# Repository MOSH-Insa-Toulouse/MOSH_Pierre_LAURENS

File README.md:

# Projet Smart Device
# MICRO-CONTROLEURS ET OPEN-SOURCE HARDWARE:
# Projet de Construction d'un capteur de gaz 
>LAURENS [Pierre](mailto:plaurens@etud.insa-toulouse.fr) - TOUZANI Ismail - Krishna Sujan

<a href="./README_EN.md">Version Anglaise</a>

Ce projet, faisant partie du Master 5ISS de l'INSA Toulouse, a été developpé dans le but de créer un capteur de gas intelligent capable de détecter plusieurs types de gas qui pourront être dangereux pour la santé humaine.
Après avoir construit le capteur dans l'atelier AIME de l'INSA, il sera donc nécessaire de le régler pour en extraire les informations utiles: cela se fera grâce au logiciel LTSpice IV pour la partie éléctronique analogique. Ensuite, et afin de récupérer les données du capteur et les communiquer à travers le réseau LoRA, on utilisera une carte Arduino Uno et une puce RN2483. Enfin, nous utiliserons le logiciel KiCAD pour effectuer le schéma adéquat du câblage entre les différents composants.

# Contenu du Projet
Le projet est constitué des répertoires suivants:
-   **Mosh (Arduino IDE)**: Contient les fichiers des tps effectués en utilisant l'IDE d'Arduino ainsi que les fichiers du projet.

-   **KiCAD**: Contient les fichiers nécessaires à la réalisation du PCB.
Ce fichier est composé de 3 dossiers.
    - **Projet Kicad** : contenant la première version de notre projet.
    - **Projet Kicad plan de masse** : contenant le même projet que le fichier ci-dessus mais avec la réalisation du plan de masse.
    - **Projet Kicad Aime plan de masse** : contenant le PCB du capteur de Gaz réalisé dans les locaux du AIME.

-   **LTSpice**: Contient les fichiers nécessaires à la partie éléctronique analogique.

-  **Manufacturing_Kicad**: Dossier contenant le fichier de création de la carte.

### Partie collection de données et communication LoRA: 
Dans cette partie, nous avons testé la collection de données et communication LoRA avec un capteur de test:

Ci-dessus l'image du montage permettant d'interconnecter le module LoRa, l'Arduino UNO et le capteur de Gaz.
Ci-dessous une série d'images montrant le résultat de notre montage avec la réception et l'envoi de la valeur du capteur.

### Partie construction du shield/PCB: 
Dans cette partie, nous avons construit notre propre shield/PCB grâce à KiCAD :

Un Zoom sur la conception du capteur de Gaz AIME sur Eeschema:

Puis ci-dessous, l'ensemble du Capteur Intelligent designé sur Eeschema:

Conception du layout avec le traçage des routes et la création des footprints et leur positionnement sur la carte.

Nous avons réalisé un plan de masse pour réduire la consommation en cuivre et limiter le routage en une seule couche. En effet, nous avons  supprimé toutes les routes sur la couche avant de notre shield(rouge) présentent sur la photo ci-dessus.
Le plan de masse permet également de réaliser le routage sur une seule couche, la couche arrière  de notre Shield. Pour finir, nous avons ainsi respecté les contraintes de routage définies par l'INSA.

### Partie électronique analogique: 
Concernant cette partie, nous avons étudier, en utilisant LTSPice IV, la partie électronique analogique du module Smart Device où nous serons amené à mesurer la résistance, le faible courant avec un microcontrôleur et effectuer un filtrage passe bas pour extraire les informations utiles de notre capteur de gaz. 

<a href="/LTspice/UF_Smart_Device_ Partie_analogique_avec_LTSpice_IV.pdf">Rapport_LTSPice</a>

### Choix de Conception

 - Nous avons modifié la forme du contour du shield en un rectangle plus grand que l'Arduino UNO pour faciliter le routage et l'inclusion de la puce LoRa.

- Au niveau du PCB, nous avons du faire face à des avertissements de type "Pad près d'un pad" au moment de la validation de notre PCB. Nous avons remarqué que ces messages ciblés les capacités que nous avons choisi dans les librairies génériques qui se sont avérés plus petites que ceux que nous utiliserons en réalité. Les marges de pistes sont trop épaisses par rapport à l'espacement entre les 2 broches des capacités provoquant un chevauchent de celles-ci entre elles. Pour changer cela, il faudrait choisir d'autres empreintes pour ces composants, car compte tenu des contraintes de fabrication qui nous sont imposées, nous ne pouvons pas réduire l'épaisseur des pistes). 

- Nous avons effectué tous les routage sur une seule couche de cuivre sur la carte pour rendre possible sa fabrication à l'INSA. Les pistes sont sur la partie "Bottom" qui est aussi le plan de masse. Les composants sont quand eux positionnés sur la partie "Top".

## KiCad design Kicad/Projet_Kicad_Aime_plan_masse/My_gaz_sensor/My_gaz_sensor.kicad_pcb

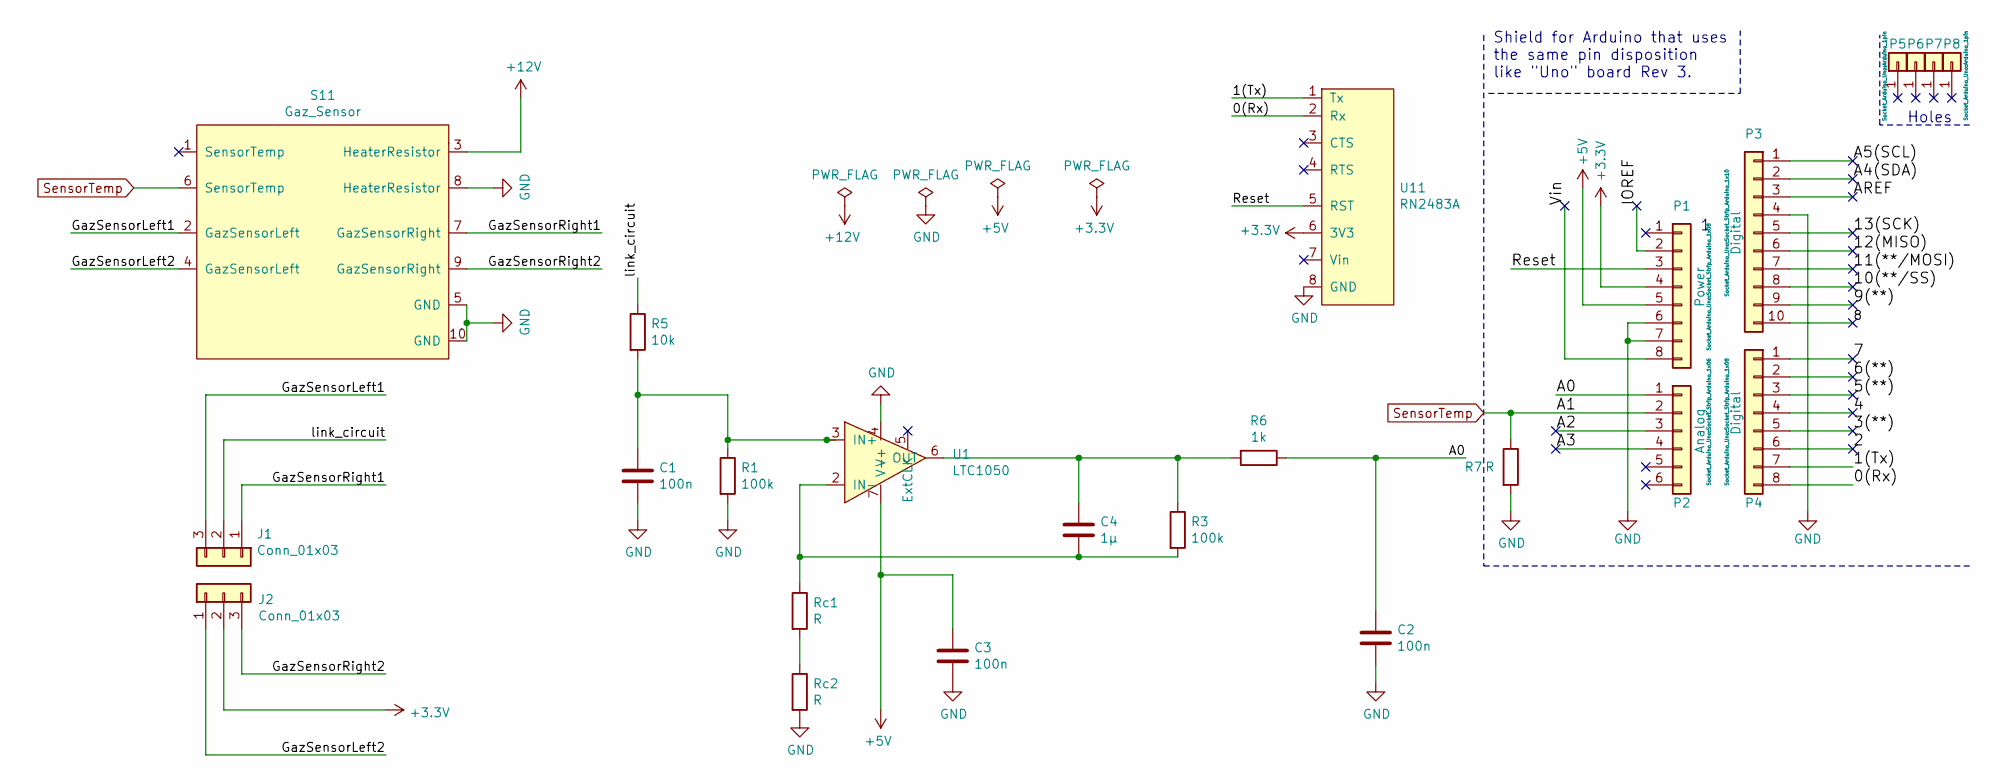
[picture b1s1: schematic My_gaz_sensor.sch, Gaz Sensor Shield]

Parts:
C1, C2, C3: 100n; C_Radial_D4.0mm_H5.0mm_P1.50mm
C4: 1µ; C_Radial_D4.0mm_H5.0mm_P1.50mm
J1, J2: Conn_01x03; PinHeader_1x03_P2.00mm_Vertical
P1: Power; Socket_Strip_Arduino_1x08
P2: Analog; Socket_Strip_Arduino_1x06
P3: Digital; Socket_Strip_Arduino_1x10
P4: Digital; Socket_Strip_Arduino_1x08
P5, P6, P7, P8: CONN_01X01; Arduino_1pin
R1, R3: 100k; R_Axial_DIN0207_L6.3mm_D2.5mm_P7.62mm_Horizontal
R5: 10k; R_Axial_DIN0207_L6.3mm_D2.5mm_P7.62mm_Horizontal
R6: 1k; R_Axial_DIN0207_L6.3mm_D2.5mm_P7.62mm_Horizontal
R7: R; R_Axial_DIN0207_L6.3mm_D2.5mm_P7.62mm_Horizontal
Rc1, Rc2: R; R_Axial_DIN0207_L6.3mm_D2.5mm_P7.62mm_Horizontal
S11: Gaz_Sensor; TO-5-10_Window
U1: LTC1050; DIP-8_W7.62mm_LongPads
U11: RN2483A; RN2483_Breakout

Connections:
+3V3: J2.2, P1.4, U11.6 (3V3)
+5V: C3.1, P1.5, U1.7 (V-)
+12V: S11.3 (HeaterResistor)
/0(Rx): P4.8, U11.2 (Rx)
/1(Tx): P4.7, U11.1 (Tx)
/2: P4.6
/3(**): P4.5
/4: P4.4
/5(**): P4.3
/6(**): P4.2
/7: P4.1
/8: P3.10
/9(**): P3.9
/10(**/SS): P3.8
/11(**/MOSI): P3.7
/12(MISO): P3.6
/13(SCK): P3.5
/A0: C2.1, P2.1, R6.1
/A2: P2.3
/A3: P2.4
/A4(SDA): P3.2
/A5(SCL): P3.1
/AREF: P3.3
/GazSensorLeft1: J1.3, S11.2 (GazSensorLeft)
/GazSensorLeft2: J2.1, S11.4 (GazSensorLeft)
/GazSensorRight1: J1.1, S11.7 (GazSensorRight)
/GazSensorRight2: J2.3, S11.9 (GazSensorRight)
/IOREF: P1.2
/Reset: P1.3, U11.5 (RST)
/Vin: P1.8
/link_circuit: J1.2, R5.1
GND: C1.2, C2.2, C3.2, P1.6, P1.7, P3.4, R1.2, R7.2, Rc2.2, S11.5 (GND), S11.8 (HeaterResistor), S11.10 (GND), U1.4 (V+), U11.8 (GND)
unnamed: C1.1, R1.1, R5.2, U1.3 (IN+)
unnamed: C4.1, R3.1, R6.2, U1.6 (OUT)
unnamed: C4.2, R3.2, Rc1.1, U1.2 (IN-)
unnamed: Rc1.2, Rc2.1
SensorTemp: P2.2, R7.1, S11.6 (SensorTemp)

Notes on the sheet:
Holes
Shield for Arduino that uses the same pin disposition like "Uno" board Rev 3.

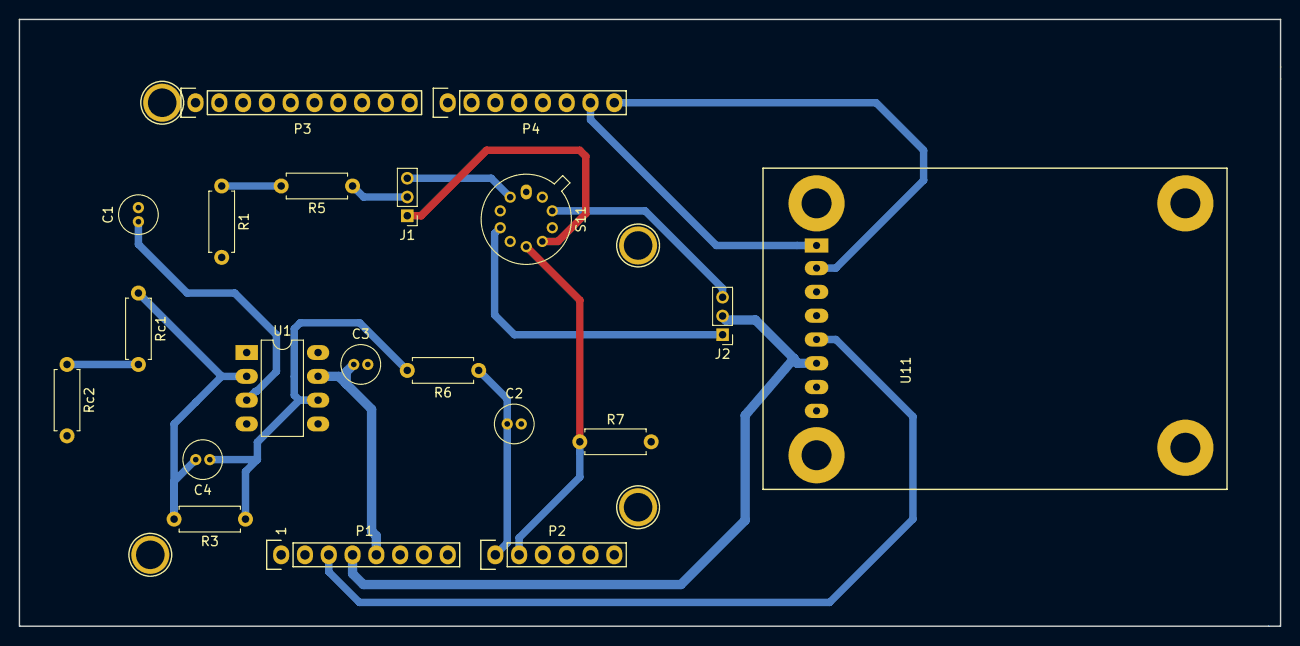
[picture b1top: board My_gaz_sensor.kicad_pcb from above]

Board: 2 copper layers, 134.6 x 64.8 mm, 24 parts (0 on the bottom side), 17 nets.

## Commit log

2019-12-11 Pierre and Ismael work
2020-01-11 Refactor of the content - Add PCB-KICAD&MOSH
2020-01-11 Kicad plan de masse et Maj Readme
2020-01-11 Ajout de la Partie électronique
2020-01-12 Ajout Image Shield final en 3D & MàJ README
2020-01-13 Modification: MàJ du dossier "Kicad"
2020-01-14 Refactor od folders
2020-01-15 MaJ README
2020-01-17 Kicad Project with AIME Gaz Sensor
2020-01-17 Add Pictures Aime sensor
2020-01-18 Refactor valeur C4
2020-01-18 MàJ des README FR et EN
2020-01-18 MàJ Images
2020-01-18 Refactor eschema capteur Gaz Aime
2020-01-18 Reduction des near-to-pad
2020-01-19 Changement pour s'adapter à la datasheet
2020-01-19 MàJ d'images
2020-01-21 Refactor Aime Kicad Part
2020-01-21 Change an image
2020-01-22 Adding the Manufacturing file
